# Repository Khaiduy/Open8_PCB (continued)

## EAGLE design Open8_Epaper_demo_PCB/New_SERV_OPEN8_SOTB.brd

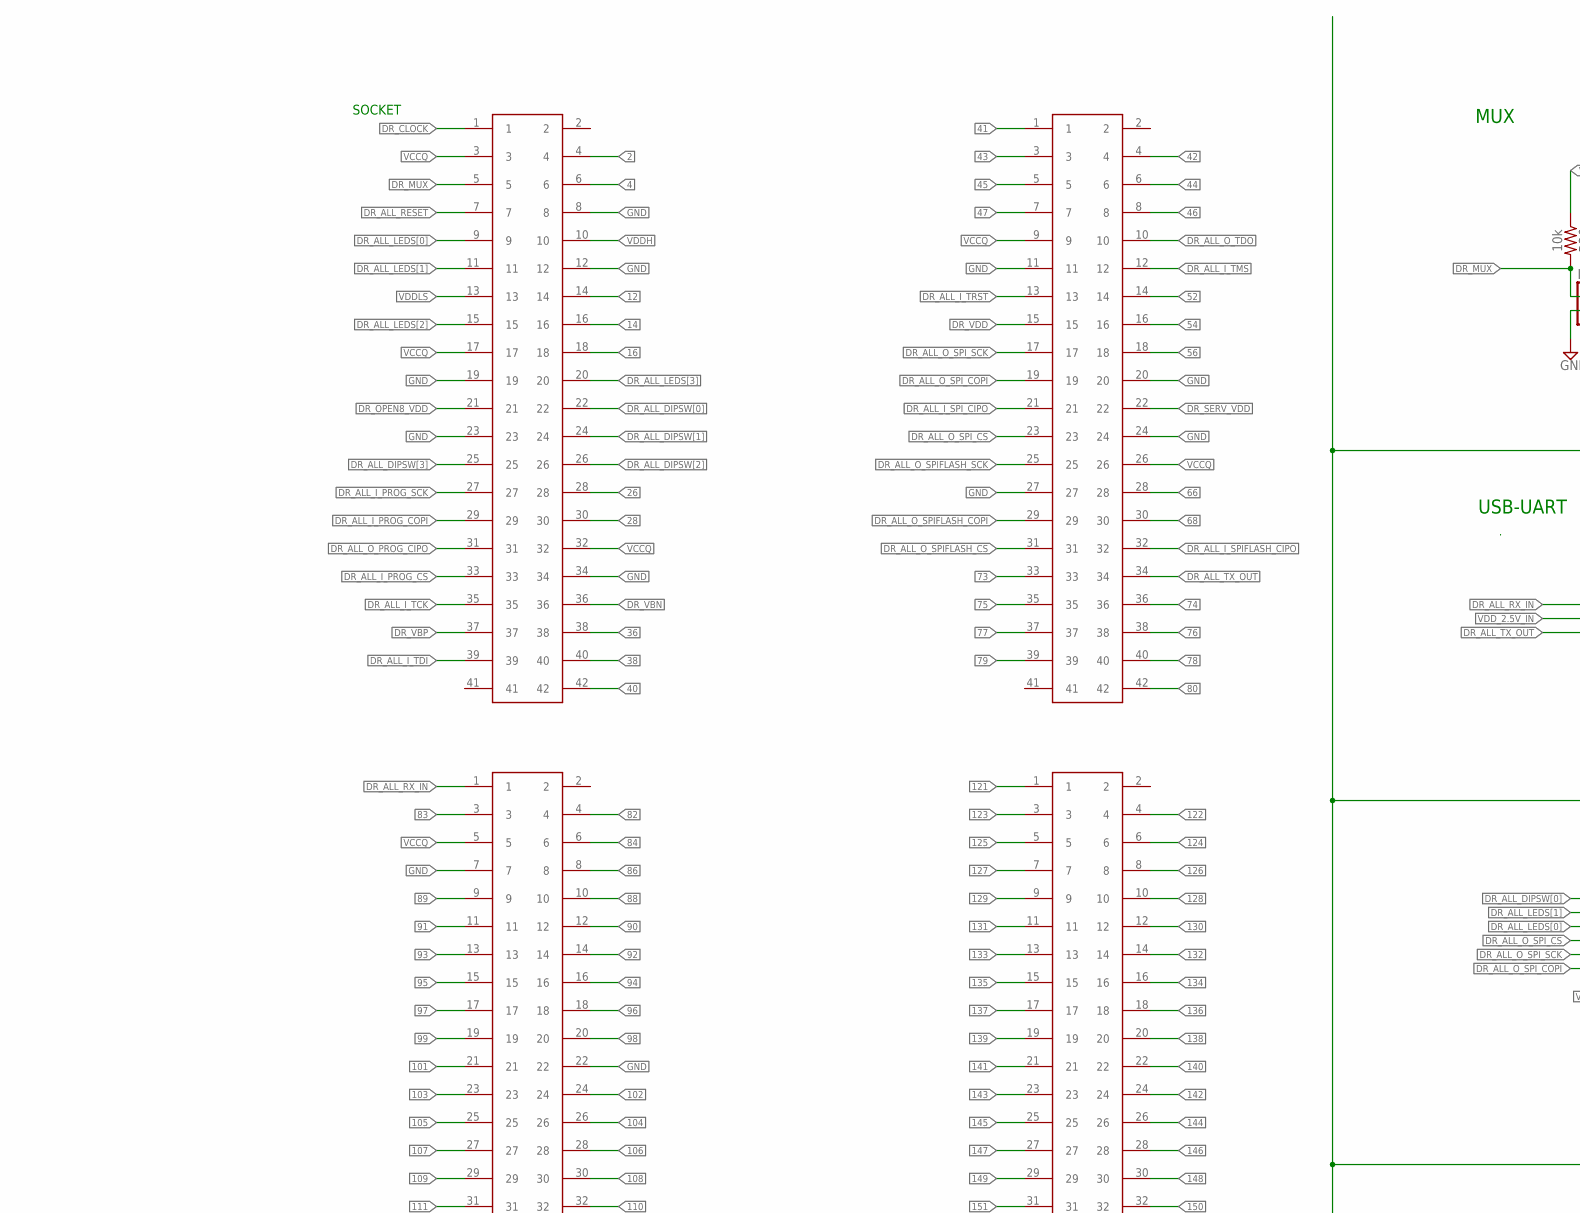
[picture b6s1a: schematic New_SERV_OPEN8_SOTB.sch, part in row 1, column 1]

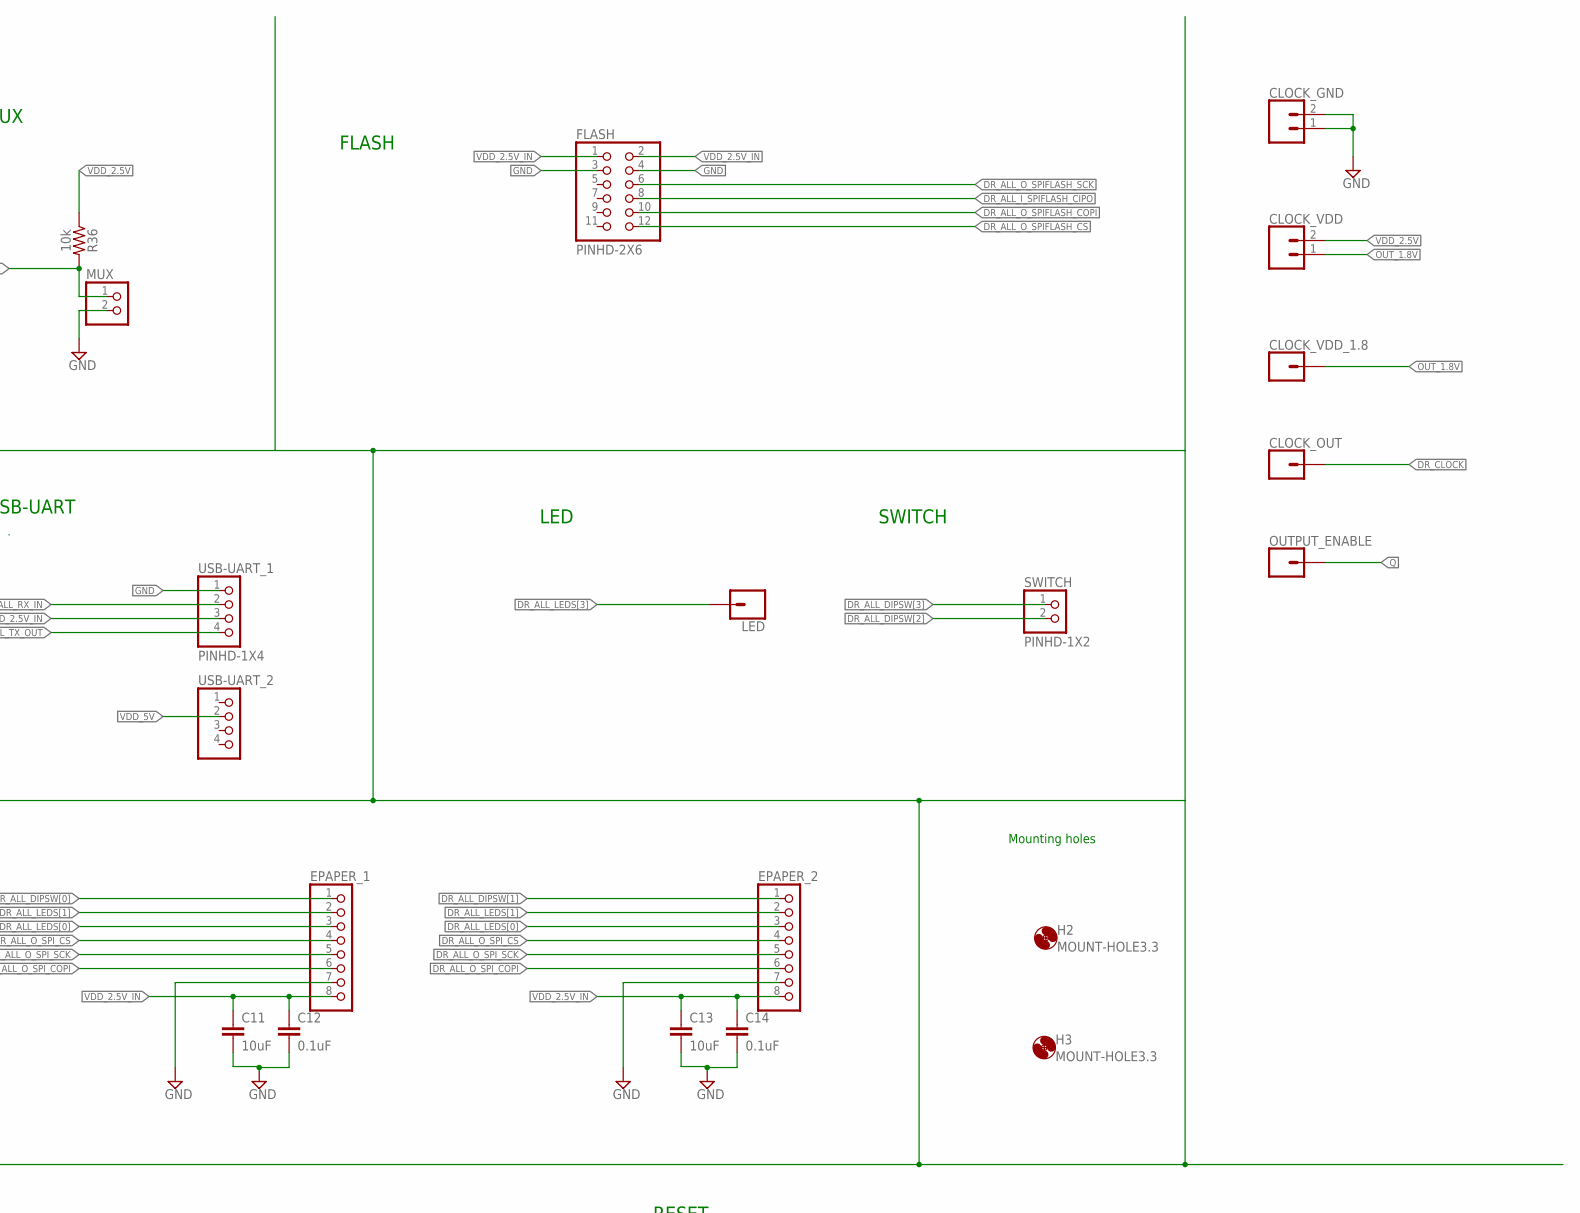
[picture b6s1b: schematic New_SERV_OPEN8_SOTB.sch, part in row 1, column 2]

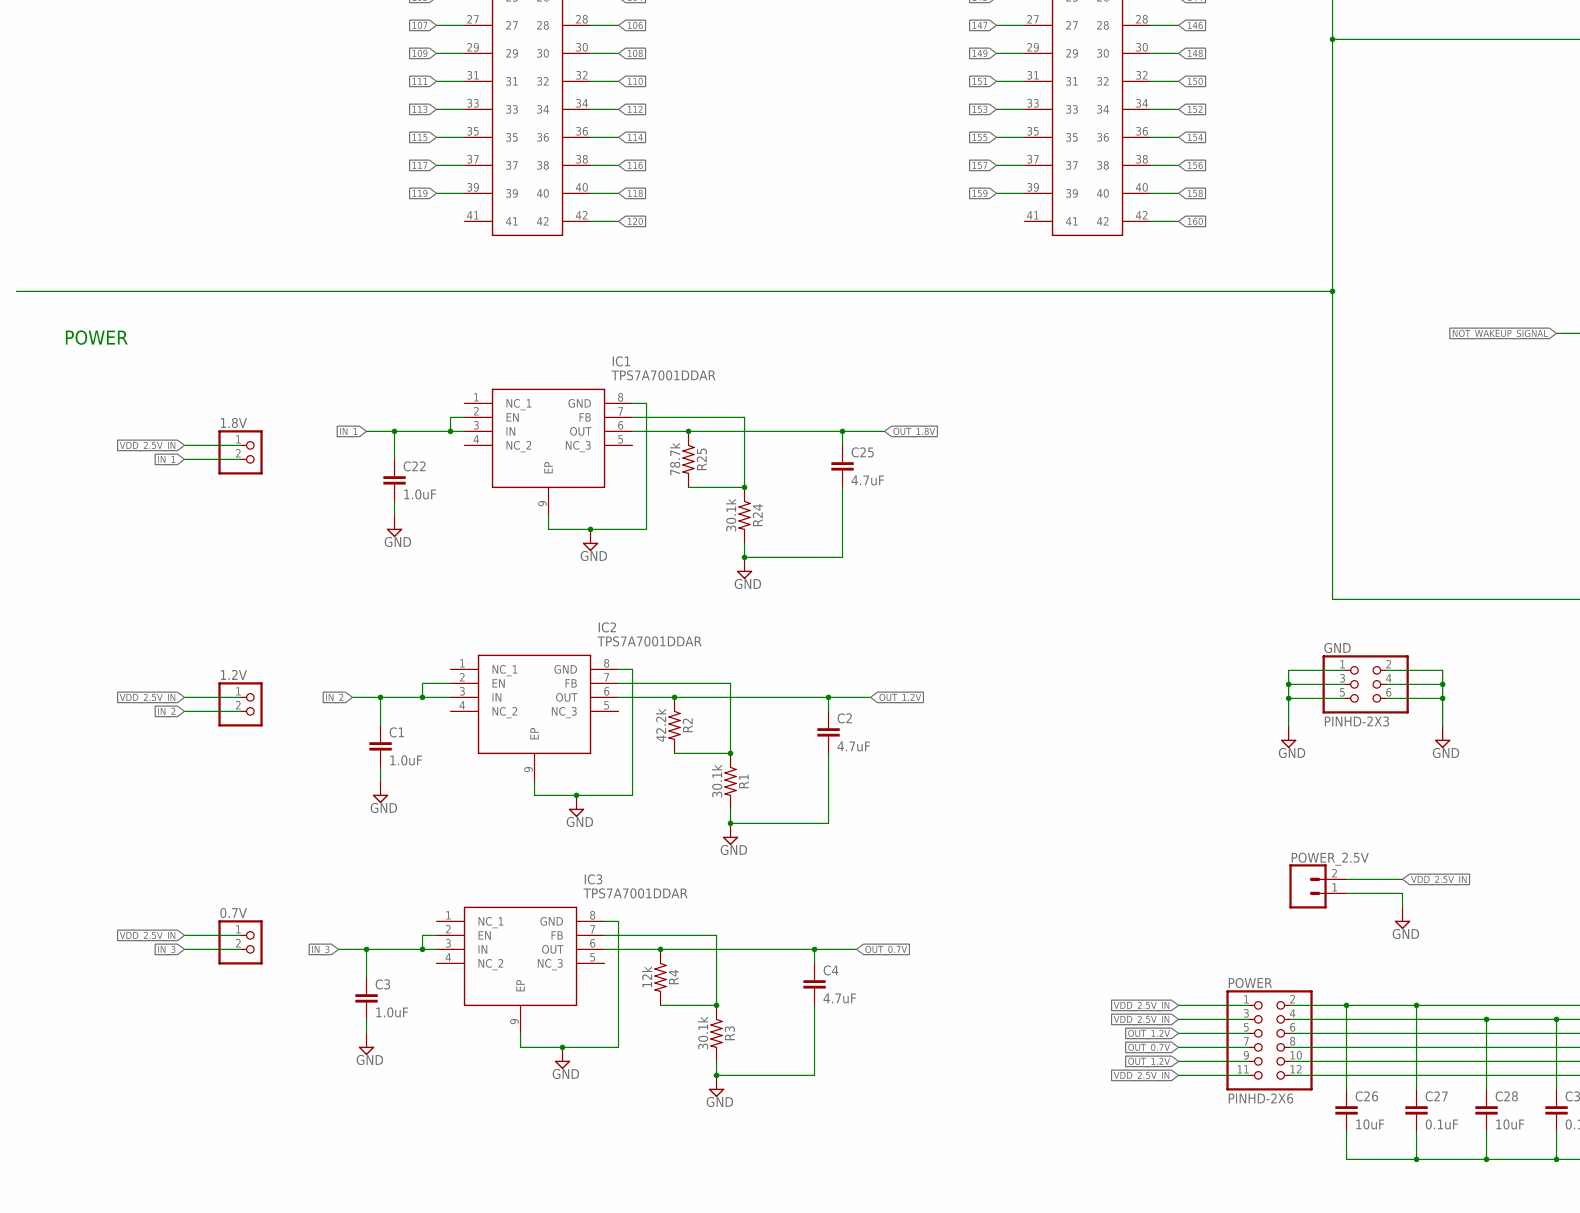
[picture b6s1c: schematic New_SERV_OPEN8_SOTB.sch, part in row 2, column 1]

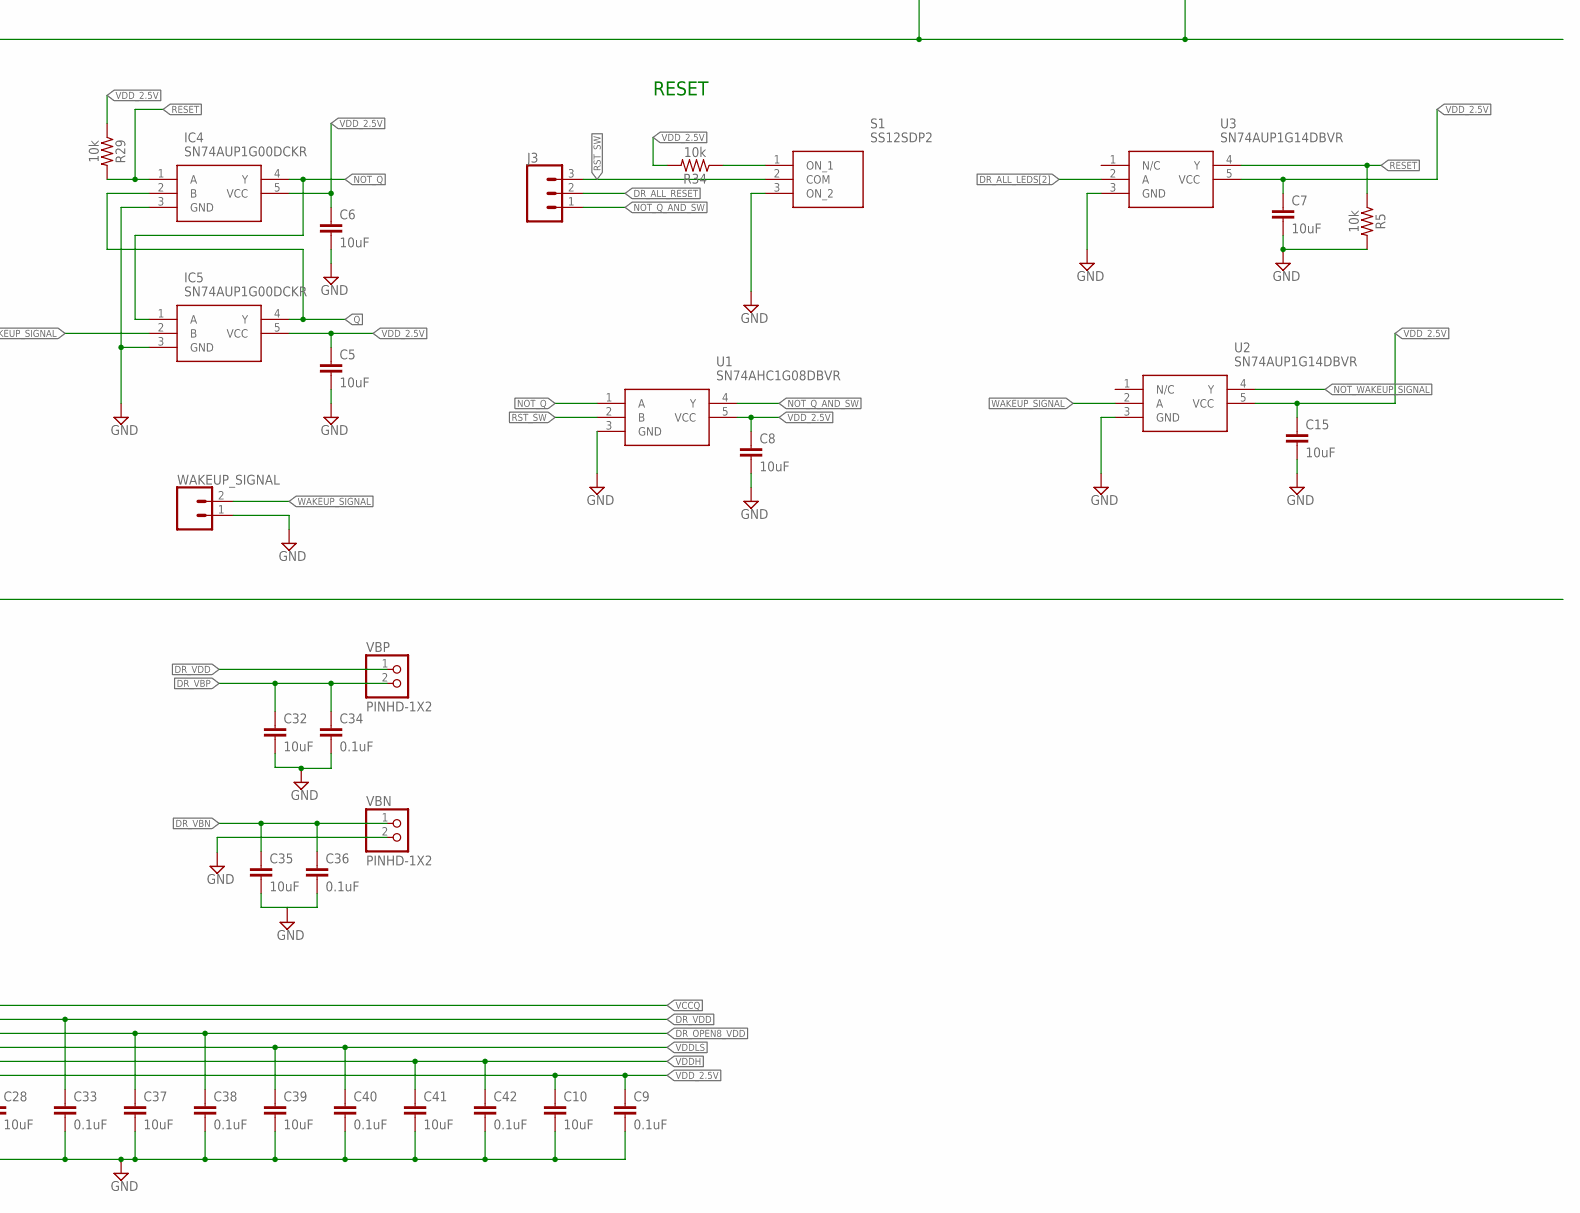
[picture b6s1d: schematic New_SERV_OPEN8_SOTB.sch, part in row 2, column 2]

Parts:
0.7V, 1.2V, 1.8V: PINHD-1X2; 1X02
C1, C3, C22: 1.0uF; 0805
C2, C4, C25: 4.7uF; 0805
C5, C6, C7, C8, C10, C11, C13, C15, C26, C28, C32, C35, C37, C39, C41: 10uF; 0805
C9, C12, C14, C27, C33, C34, C36, C38, C40, C42: 0.1uF; 0805
CLOCK_GND: CONN_02; 1X02
CLOCK_OUT: CONN_01; 1X01
CLOCK_VDD: CONN_02; 1X02
CLOCK_VDD_1.8: CONN_01; 1X01
EPAPER_1, EPAPER_2: PINHD-1X8; 1X08
FLASH: PINHD-2X6; 2X06
GND: PINHD-2X3; 2X03
H2, H3: MOUNT-HOLE3.3; 3,3
IC1, IC2, IC3: TPS7A7001DDAR; SOIC127P600X170-9N
IC4, IC5: SN74AUP1G00DCKR; SOT65P210X110-5N
J3: CONN_03; 1X03
LED: CONN_01; 1X01
MUX: PINHD-1X2; 1X02
OUTPUT_ENABLE: CONN_01; 1X01
POWER: PINHD-2X6; 2X06
POWER_2.5V: CONN_02; 1X02
R1, R3, R24: 30.1k; 0805
R2: 42.2k; 0805
R4: 12k; 0805
R5, R29, R34, R36: 10k; 0805
R25: 78.7k; 0805
S1: SS12SDP2
SWITCH: PINHD-1X2; 1X02
U1: SN74AHC1G08DBVR; SOT95P280X145-5N
U2, U3: SN74AUP1G14DBVR; SOT65P210X110-5N
U$1, U$2, U$3, U$4: 2X41_HEADER
USB-UART_1, USB-UART_2: PINHD-1X4; 1X04
VBN: PINHD-1X2; 1X02
VBP: PINHD-1X2; 1X02
WAKEUP_SIGNAL: CONN_02; 1X02

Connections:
2: U$1.4
4: U$1.6
12: U$1.14
14: U$1.16
16: U$1.18
26: U$1.28
28: U$1.30
36: U$1.38
38: U$1.40
40: U$1.42
41: U$2.1
42: U$2.4
43: U$2.3
44: U$2.6
45: U$2.5
46: U$2.8
47: U$2.7
52: U$2.14
54: U$2.16
56: U$2.18
66: U$2.28
68: U$2.30
73: U$2.33
74: U$2.36
75: U$2.35
76: U$2.38
77: U$2.37
78: U$2.40
79: U$2.39
80: U$2.42
82: U$3.4
83: U$3.3
84: U$3.6
86: U$3.8
88: U$3.10
89: U$3.9
90: U$3.12
91: U$3.11
92: U$3.14
93: U$3.13
94: U$3.16
95: U$3.15
96: U$3.18
97: U$3.17
98: U$3.20
99: U$3.19
101: U$3.21
102: U$3.24
103: U$3.23
104: U$3.26
105: U$3.25
106: U$3.28
107: U$3.27
108: U$3.30
109: U$3.29
110: U$3.32
111: U$3.31
112: U$3.34
113: U$3.33
114: U$3.36
115: U$3.35
116: U$3.38
117: U$3.37
118: U$3.40
119: U$3.39
120: U$3.42
121: U$4.1
122: U$4.4
123: U$4.3
124: U$4.6
125: U$4.5
126: U$4.8
127: U$4.7
128: U$4.10
129: U$4.9
130: U$4.12
131: U$4.11
132: U$4.14
133: U$4.13
134: U$4.16
135: U$4.15
136: U$4.18
137: U$4.17
138: U$4.20
139: U$4.19
140: U$4.22
141: U$4.21
142: U$4.24
143: U$4.23
144: U$4.26
145: U$4.25
146: U$4.28
147: U$4.27
148: U$4.30
149: U$4.29
150: U$4.32
151: U$4.31
152: U$4.34
153: U$4.33
154: U$4.36
155: U$4.35
156: U$4.38
157: U$4.37
158: U$4.40
159: U$4.39
160: U$4.42
DR_ALL_DIPSW[0]: EPAPER_1.1, U$1.22
DR_ALL_DIPSW[1]: EPAPER_2.1, U$1.24
DR_ALL_DIPSW[2]: SWITCH.2, U$1.26
DR_ALL_DIPSW[3]: SWITCH.1, U$1.25
DR_ALL_I_PROG_COPI: U$1.29
DR_ALL_I_PROG_CS: U$1.33
DR_ALL_I_PROG_SCK: U$1.27
DR_ALL_I_SPIFLASH_CIPO: FLASH.8, U$2.32
DR_ALL_I_SPI_CIPO: U$2.21
DR_ALL_I_TCK: U$1.35
DR_ALL_I_TDI: U$1.39
DR_ALL_I_TMS: U$2.12
DR_ALL_I_TRST: U$2.13
DR_ALL_LEDS[0]: EPAPER_1.3, EPAPER_2.3, U$1.9
DR_ALL_LEDS[1]: EPAPER_1.2, EPAPER_2.2, U$1.11
DR_ALL_LEDS[2]: U3.2 (A), U$1.15
DR_ALL_LEDS[3]: LED.1, U$1.20
DR_ALL_O_PROG_CIPO: U$1.31
DR_ALL_O_SPIFLASH_COPI: FLASH.10, U$2.29
DR_ALL_O_SPIFLASH_CS: FLASH.12, U$2.31
DR_ALL_O_SPIFLASH_SCK: FLASH.6, U$2.25
DR_ALL_O_SPI_COPI: EPAPER_1.6, EPAPER_2.6, U$2.19
DR_ALL_O_SPI_CS: EPAPER_1.4, EPAPER_2.4, U$2.23
DR_ALL_O_SPI_SCK: EPAPER_1.5, EPAPER_2.5, U$2.17
DR_ALL_O_TDO: U$2.10
DR_ALL_RESET: J3.2, U$1.7
DR_ALL_RX_IN: U$3.1, USB-UART_1.2
DR_ALL_TX_OUT: U$2.34, USB-UART_1.4
DR_CLOCK: CLOCK_OUT.1, U$1.1
DR_MUX: MUX.1, R36.2, U$1.5
DR_OPEN8_VDD: C37.1, C38.1, POWER.6, U$1.21
DR_SERV_VDD: U$2.22
DR_VBN: C35.1, C36.1, U$1.36, VBN.1
DR_VBP: C32.1, C34.1, U$1.37, VBP.2
DR_VDD: C28.1, C33.1, POWER.4, U$2.15, VBP.1
GND: C1.2, C2.2, C3.2, C4.2, C5.2, C6.2, C7.2, C8.2, C9.2, C10.2, C11.2, C12.2, C13.2, C14.2, C15.2, C22.2, C25.2, C26.2, C27.2, C28.2, C32.2, C33.2, C34.2, C35.2, C36.2, C37.2, C38.2, C39.2, C40.2, C41.2, C42.2, CLOCK_GND.1, CLOCK_GND.2, EPAPER_1.7, EPAPER_2.7, FLASH.3, FLASH.4, GND.1, GND.2, GND.3, GND.4, GND.5, GND.6, IC1.8 (GND), IC1.9 (EP), IC2.8 (GND), IC2.9 (EP), IC3.8 (GND), IC3.9 (EP), IC4.3 (GND), IC5.3 (GND), MUX.2, POWER_2.5V.1, R1.2, R3.2, R5.2, R24.2, S1.3 (ON_2), U1.3 (GND), U2.3 (GND), U3.3 (GND), U$1.8, U$1.12, U$1.19, U$1.23, U$1.34, U$2.11, U$2.20, U$2.24, U$2.27, U$3.7, U$3.22, USB-UART_1.1, VBN.2, WAKEUP_SIGNAL.1
IN_1: 1.8V.2, C22.1, IC1.2 (EN), IC1.3 (IN)
IN_2: 1.2V.2, C1.1, IC2.2 (EN), IC2.3 (IN)
IN_3: 0.7V.2, C3.1, IC3.2 (EN), IC3.3 (IN)
unnamed: IC2.7 (FB), R1.1, R2.2
unnamed: IC3.7 (FB), R3.1, R4.2
unnamed: R34.1, S1.1 (ON_1)
unnamed: IC1.7 (FB), R24.1, R25.2
NOT_Q: IC4.4 (Y), IC5.1 (A), U1.1 (A)
NOT_Q_AND_SW: J3.1, U1.4 (Y)
NOT_WAKEUP_SIGNAL: IC5.2 (B), U2.4 (Y)
OUT_0.7V: C4.1, IC3.6 (OUT), POWER.7, R4.1
OUT_1.2V: C2.1, IC2.6 (OUT), POWER.5, POWER.9, R2.1
OUT_1.8V: C25.1, CLOCK_VDD.1, CLOCK_VDD_1.8.1, IC1.6 (OUT), R25.1
Q: IC4.2 (B), IC5.4 (Y), OUTPUT_ENABLE.1
RESET: IC4.1 (A), R5.1, R29.2, U3.4 (Y)
RST_SW: J3.3, S1.2 (COM), U1.2 (B)
VCCQ: C26.1, C27.1, POWER.2, U$1.3, U$1.17, U$1.32, U$2.9, U$2.26, U$3.5
VDDH: C41.1, C42.1, POWER.10, U$1.10
VDDLS: C39.1, C40.1, POWER.8, U$1.13
VDD_2.5V: C5.1, C6.1, C7.1, C8.1, C9.1, C10.1, C15.1, CLOCK_VDD.2, IC4.5 (VCC), IC5.5 (VCC), POWER.12, R29.1, R34.2, R36.1, U1.5 (VCC), U2.5 (VCC), U3.5 (VCC)
VDD_2.5V_IN: 0.7V.1, 1.2V.1, 1.8V.1, C11.1, C12.1, C13.1, C14.1, EPAPER_1.8, EPAPER_2.8, FLASH.1, FLASH.2, POWER.1, POWER.3, POWER.11, POWER_2.5V.2, USB-UART_1.3
VDD_5V: USB-UART_2.2
WAKEUP_SIGNAL: U2.2 (A), WAKEUP_SIGNAL.2

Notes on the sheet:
SOCKET
RESET
Mounting holes
MUX
FLASH
USB-UART
LED
SWITCH
POWER

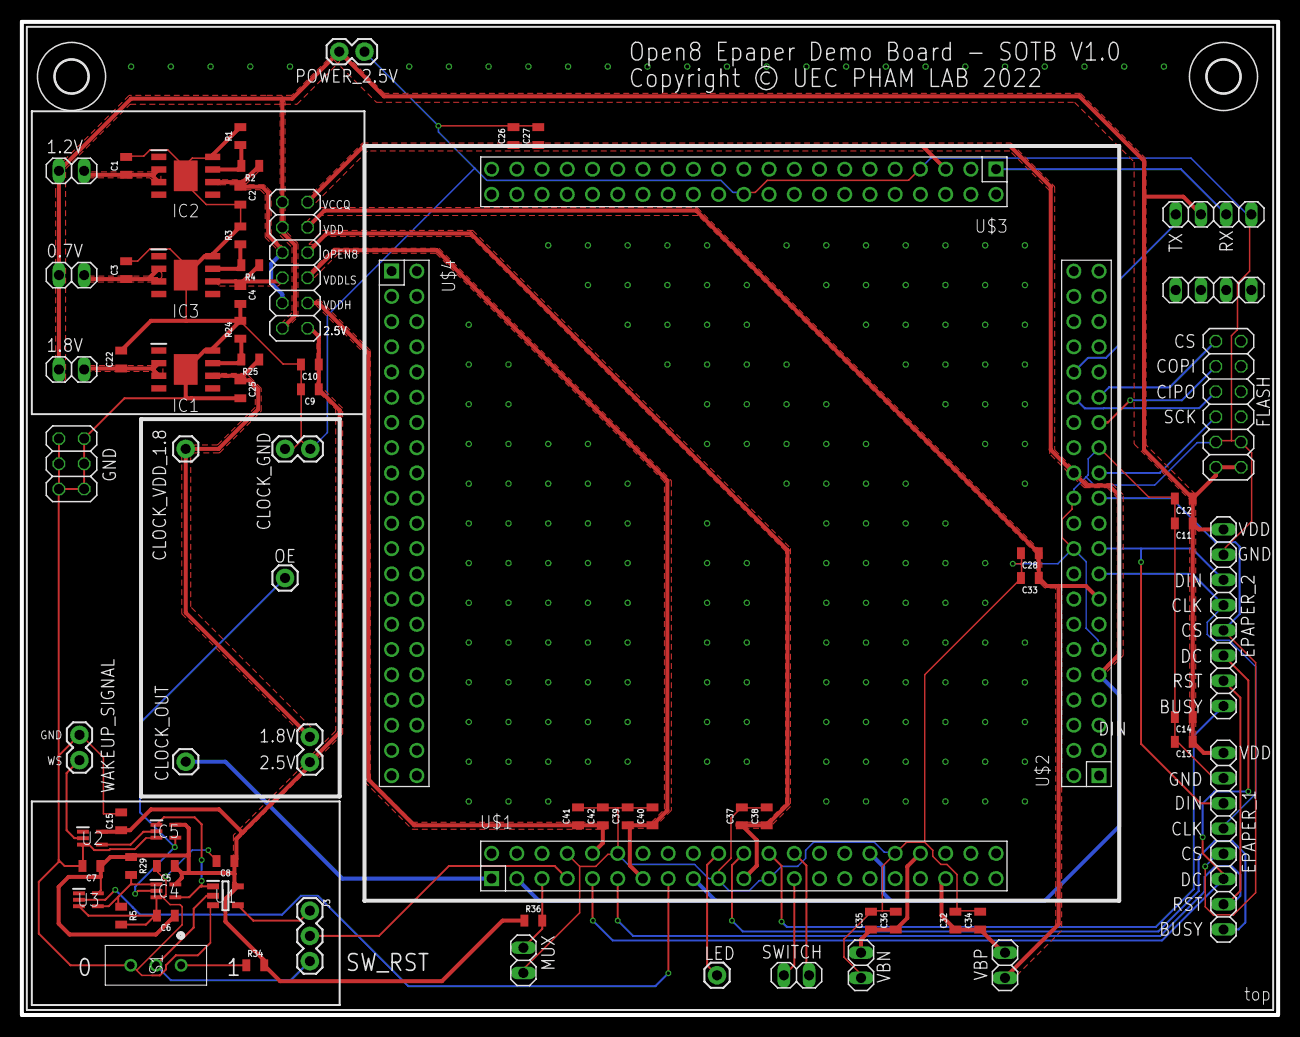
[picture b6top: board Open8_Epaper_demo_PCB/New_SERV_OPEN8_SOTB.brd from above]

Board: 2 copper layers, 126.5 x 100.0 mm, 79 parts (0 on the bottom side), 47 nets.

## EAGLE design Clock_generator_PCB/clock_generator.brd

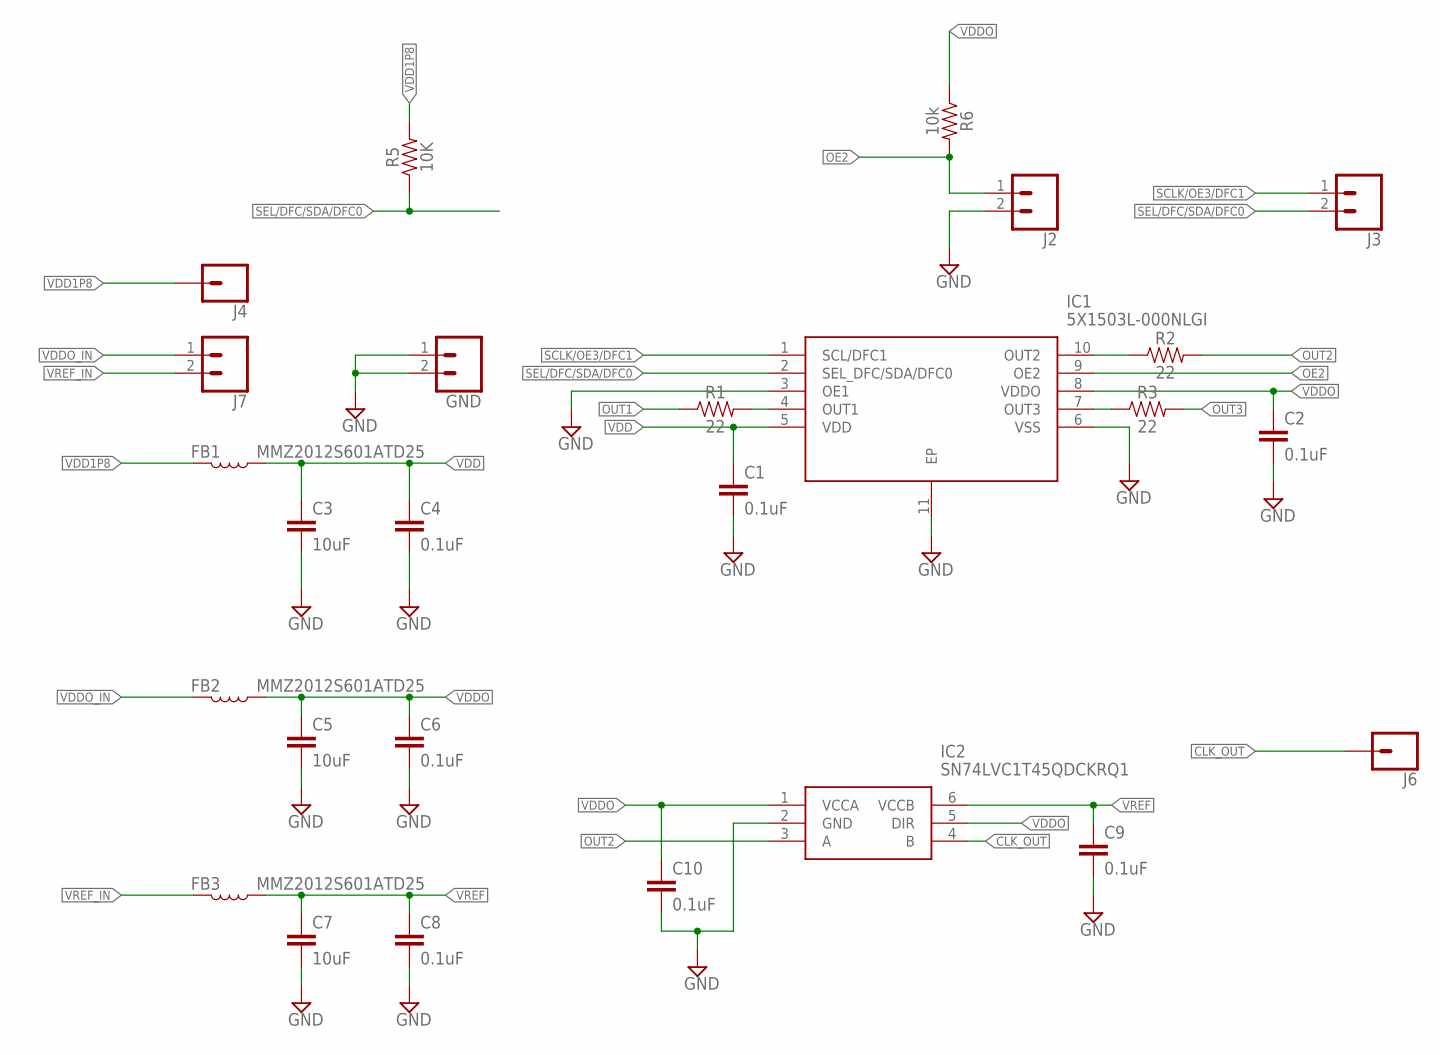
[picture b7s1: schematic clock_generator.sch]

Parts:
C1, C2, C4, C6, C8, C9, C10: 0.1uF; 0805
C3, C5, C7: 10uF; 0805
FB1, FB2, FB3: MMZ2012S601ATD25; 0805
GND: CONN_02; 1X02
IC1: 5X1503L-000NLGI; SON40P200X200X110-11N
IC2: SN74LVC1T45QDCKRQ1; SOT65P210X110-6N
J2, J3, J7: CONN_02; 1X02
J4, J6: CONN_01; 1X01
R1, R2, R3: 22; 0805
R5: 10K; 0805
R6: 10k; 0805

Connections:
CLK_OUT: IC2.4 (B), J6.1
GND: C1.2, C2.2, C3.2, C4.2, C5.2, C6.2, C7.2, C8.2, C9.2, C10.2, GND.1, GND.2, IC1.3 (OE1), IC1.6 (VSS), IC1.11 (EP), IC2.2 (GND), J2.2
unnamed: IC1.7 (OUT3), R3.1
unnamed: IC1.4 (OUT1), R1.2
unnamed: IC1.10 (OUT2), R2.1
OE2: IC1.9 (OE2), J2.1, R6.2
OUT1: R1.1
OUT2: IC2.3 (A), R2.2
OUT3: R3.2
SCLK/OE3/DFC1: IC1.1 (SCL/DFC1), J3.1
SEL/DFC/SDA/DFC0: IC1.2 (SEL_DFC/SDA/DFC0), J3.2, R5.1
VDD: C1.1, C3.1, C4.1, FB1.1, IC1.5 (VDD)
VDD1P8: FB1.2, J4.1, R5.2
VDDO: C2.1, C5.1, C6.1, C10.1, FB2.1, IC1.8 (VDDO), IC2.1 (VCCA), IC2.5 (DIR), R6.1
VDDO_IN: FB2.2, J7.1
VREF: C7.1, C8.1, C9.1, FB3.1, IC2.6 (VCCB)
VREF_IN: FB3.2, J7.2

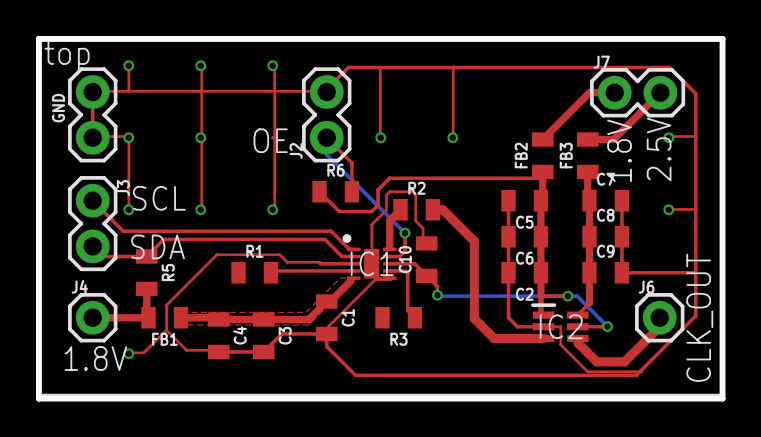
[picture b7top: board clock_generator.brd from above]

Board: 2 copper layers, 38.0 x 20.0 mm, 26 parts (0 on the bottom side), 15 nets.

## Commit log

2021-05-26 initial begin
2021-05-26 add libraries
2021-05-31 Connect source for switches
2021-05-31 Organize regulator circuits
2021-05-31 Check USB and UART
2021-05-31 Update layout
2021-06-01 Create plain for power wires
2021-06-01 Update polygons
2021-06-01 Update layout again
2021-06-01 Add more via for power connection
2021-06-04 Organize the schematic and the layout
2021-06-07 Add 4 holes for the screws
2021-06-07 Update again schematic for consistency
2021-06-07 update library
2021-06-08 change as Duran's suggest
2021-06-08 change BJT to MOSFET for power leds
2021-06-09 Update again with Duran's suggest
2021-06-10 change USB connector
2021-06-29 Add qfp160 socket and open8 board for SOTB
2021-07-06 add pin numbers for the socket
2021-07-09 Add BOM and CPL files
2021-08-18 Update schematic for TR4 PCB
2021-09-13 Add pull resistor for mosfet
2021-09-27 new schematic and layout from Thuc's suggestion
2021-09-30 Update signal name and connect pin 59 and 60
2021-10-01 put header for param[0] signal
2021-10-01 update file
    update BOM, position, and Gerber file, change the footprint of the level shifter
2021-10-01 update for order
2021-10-01 update gerber file
2021-10-01 add Gerber for socket
2021-11-01 Update PCB for Open8 & SERV of TSMC and ROHM
2021-11-01 Update new socket PCB for the QFP160
2021-11-15 Update gerber, bom and position file for PCB
2021-11-15 Change in position of Jtag connector
2021-11-15 Update cpl file
2021-12-20 Update PCB of Dao, change switch resistor to 0805
2021-12-21 change led from white to green
2021-12-21 update boom and gerber file
2021-12-21 Upload 20pin jtag to pmod adapter
2022-01-04 Update new PCB for the TEE
2022-01-06 Change regulators for higher current
2022-01-07 Update new footprint for Lora module
2022-01-11 Update boom file
2022-01-12 Update new bom
2022-02-02 Update new regulators
2022-07-05 Upload clock generator and epaper demo board
2022-08-12 Add PCB for the Rocket32_TRASIO
2022-08-29 Upload BOM and gerber files
2022-08-30 Update the new n channel mosfet
2022-09-18 Upload new TRASIO PCB with some fixes
2022-09-18 Update position of Flash
2022-09-22 Fix SD card position
2022-09-25 Update position of SD card again
2022-09-27 This should work man
2022-09-30 demo PCB for epaper
2022-09-30 add trimmer
2022-09-30 update the cpl
2022-10-27 Upload PCB for new ROHM (Rocket + SERV + LEROS)
2022-10-27 Update pdf for schematic of ROHM102022
2022-10-29 Connect JTAG to FPGA
2022-11-16 Upload new PCB schematic for SOTB Feb.2022
2022-11-16 Update the pcb of SOTB Feb2022
2022-11-18 Update the PCB with layout
2022-12-02 Upload bom and cpl
2023-01-12 Upload PCB for SOTB LWC of Ronaldo
2023-01-13 Upload bom and cpl file for SOTB LWC Jan.2023
2023-01-13 Change led from 1206 to 0805
2023-04-18 upload pin map for lwc pcb
2023-07-26 add pdf for schematic
2024-07-09 add 160pin Aitendo and Sapporo connector footprint
